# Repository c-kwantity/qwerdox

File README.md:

# Qwerdox Keyboard

Qwerdox is my own fork of the [Kudox keyboard](https://github.com/kumaokobo/kudox-keyboard)

The idea was to learn keyboard PCB design and to design a keyboard with more thumb keys and an additional row of keys that can be mapped to various functions.

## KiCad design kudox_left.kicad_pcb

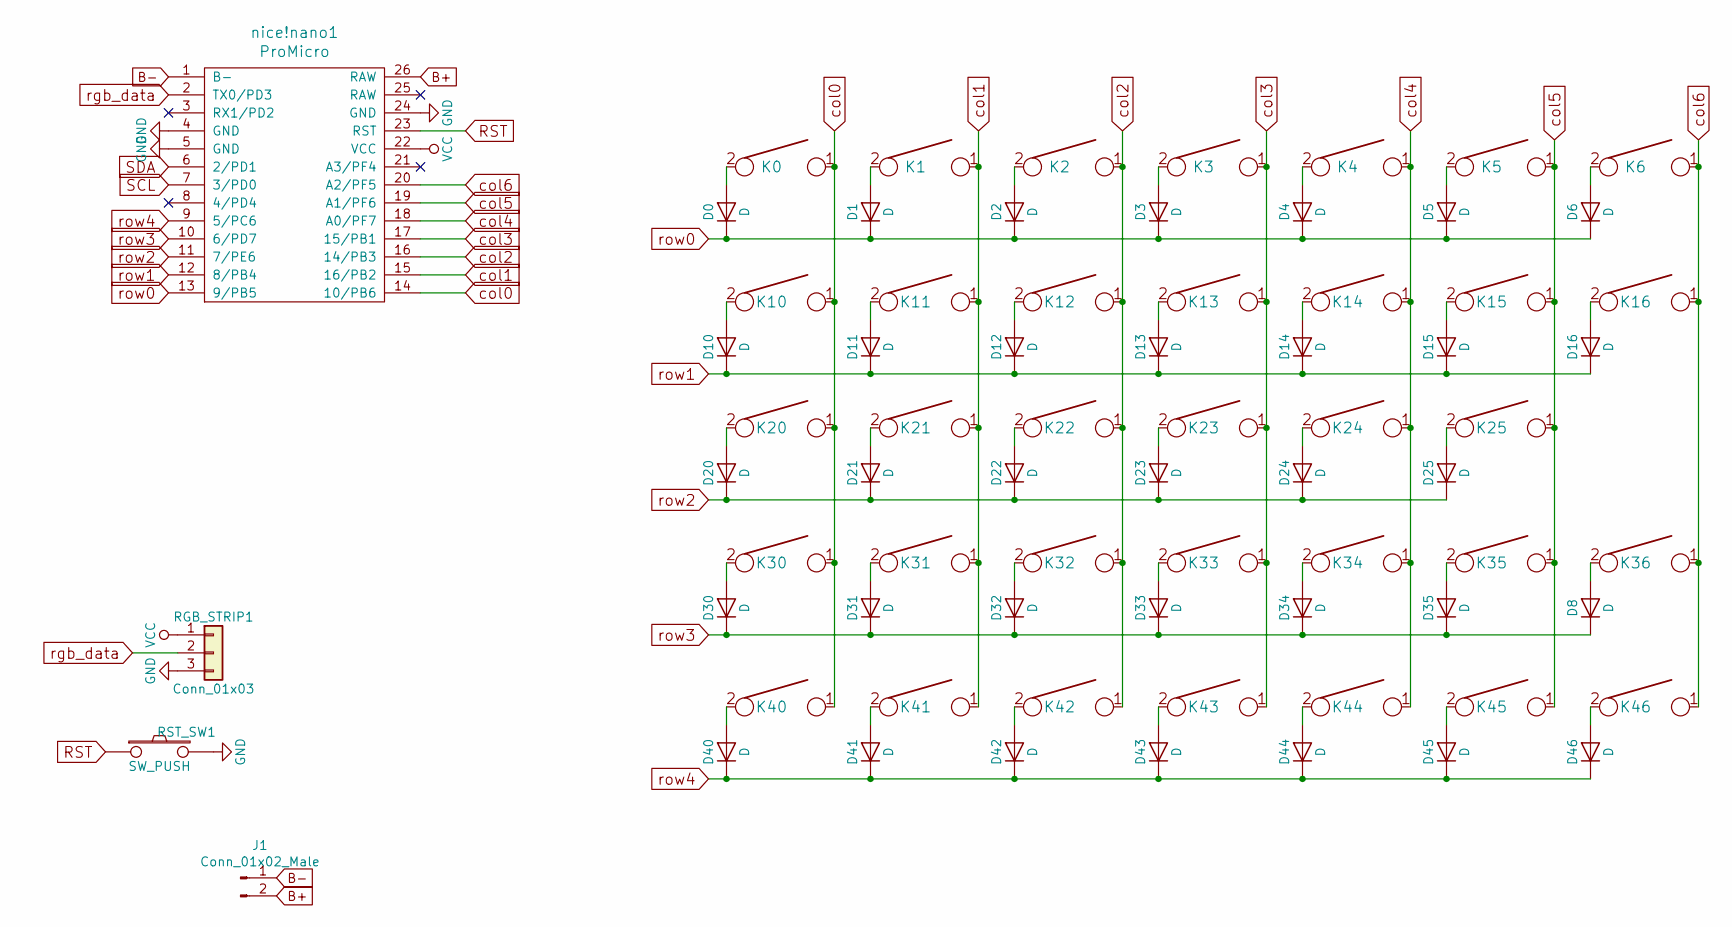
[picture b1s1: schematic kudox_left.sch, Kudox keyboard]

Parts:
D0, D1, D2, D3, D4, D5, D6, D8, D10, D11, D12, D13, D14, D15, D16, D20, D21, D22, D23, D24, D25, D30, D31, D32, D33, D34, D35, D40, D41, D42, D43, D44, D45, D46: D; Diode-dual
J1: Conn_01x02_Male; Molex_KK-254_AE-6410-02A_1x02_P2.54mm_Vertical
K0, K1, K2, K3, K4, K5, K6, K10, K11, K12, K13, K14, K15, K16, K20, K21, K22, K23, K24, K25, K30, K31, K32, K33, K34, K35, K36, K40, K41, K42, K43, K44, K45, K46: KEYSW; MXOnly-1U-Hotswap
RGB_STRIP1: Conn_01x03; Molex_KK-254_AE-6410-03A_1x03_P2.54mm_Vertical
RST_SW1: SW_PUSH; SW_PUSH_6mm_h4.3mm
nice!nano1: ProMicro; ArduinoProMicro

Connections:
B+: J1.2, nice!nano1.26 (RAW)
B-: J1.1, nice!nano1.1 (B-)
GND: RGB_STRIP1.3, RST_SW1.2, nice!nano1.4 (GND), nice!nano1.5 (GND), nice!nano1.24 (GND)
unnamed: D0.2 (A), K0.2
unnamed: D1.2 (A), K1.2
unnamed: D2.2 (A), K2.2
unnamed: D3.2 (A), K3.2
unnamed: D4.2 (A), K4.2
unnamed: D5.2 (A), K5.2
unnamed: D6.2 (A), K6.2
unnamed: D8.2 (A), K36.2
unnamed: D10.2 (A), K10.2
unnamed: D11.2 (A), K11.2
unnamed: D12.2 (A), K12.2
unnamed: D13.2 (A), K13.2
unnamed: D14.2 (A), K14.2
unnamed: D15.2 (A), K15.2
unnamed: D16.2 (A), K16.2
unnamed: D20.2 (A), K20.2
unnamed: D21.2 (A), K21.2
unnamed: D22.2 (A), K22.2
unnamed: D23.2 (A), K23.2
unnamed: D24.2 (A), K24.2
unnamed: D25.2 (A), K25.2
unnamed: D30.2 (A), K30.2
unnamed: D31.2 (A), K31.2
unnamed: D32.2 (A), K32.2
unnamed: D33.2 (A), K33.2
unnamed: D34.2 (A), K34.2
unnamed: D35.2 (A), K35.2
unnamed: D40.2 (A), K40.2
unnamed: D41.2 (A), K41.2
unnamed: D42.2 (A), K42.2
unnamed: D43.2 (A), K43.2
unnamed: D44.2 (A), K44.2
unnamed: D45.2 (A), K45.2
unnamed: D46.2 (A), K46.2
RST: RST_SW1.1, nice!nano1.23 (RST)
VCC: RGB_STRIP1.1, nice!nano1.22 (VCC)
col0: K0.1, K10.1, K20.1, K30.1, K40.1, nice!nano1.14 (10/PB6)
col1: K1.1, K11.1, K21.1, K31.1, K41.1, nice!nano1.15 (16/PB2)
col2: K2.1, K12.1, K22.1, K32.1, K42.1, nice!nano1.16 (14/PB3)
col3: K3.1, K13.1, K23.1, K33.1, K43.1, nice!nano1.17 (15/PB1)
col4: K4.1, K14.1, K24.1, K34.1, K44.1, nice!nano1.18 (A0/PF7)
col5: K5.1, K15.1, K25.1, K35.1, K45.1, nice!nano1.19 (A1/PF6)
col6: K6.1, K16.1, K36.1, K46.1, nice!nano1.20 (A2/PF5)
rgb_data: RGB_STRIP1.2, nice!nano1.2 (TX0/PD3)
row0: D0.1 (K), D1.1 (K), D2.1 (K), D3.1 (K), D4.1 (K), D5.1 (K), D6.1 (K), nice!nano1.13 (9/PB5)
row1: D10.1 (K), D11.1 (K), D12.1 (K), D13.1 (K), D14.1 (K), D15.1 (K), D16.1 (K), nice!nano1.12 (8/PB4)
row2: D20.1 (K), D21.1 (K), D22.1 (K), D23.1 (K), D24.1 (K), D25.1 (K), nice!nano1.11 (7/PE6)
row3: D8.1 (K), D30.1 (K), D31.1 (K), D32.1 (K), D33.1 (K), D34.1 (K), D35.1 (K), nice!nano1.10 (6/PD7)
row4: D40.1 (K), D41.1 (K), D42.1 (K), D43.1 (K), D44.1 (K), D45.1 (K), D46.1 (K), nice!nano1.9 (5/PC6)

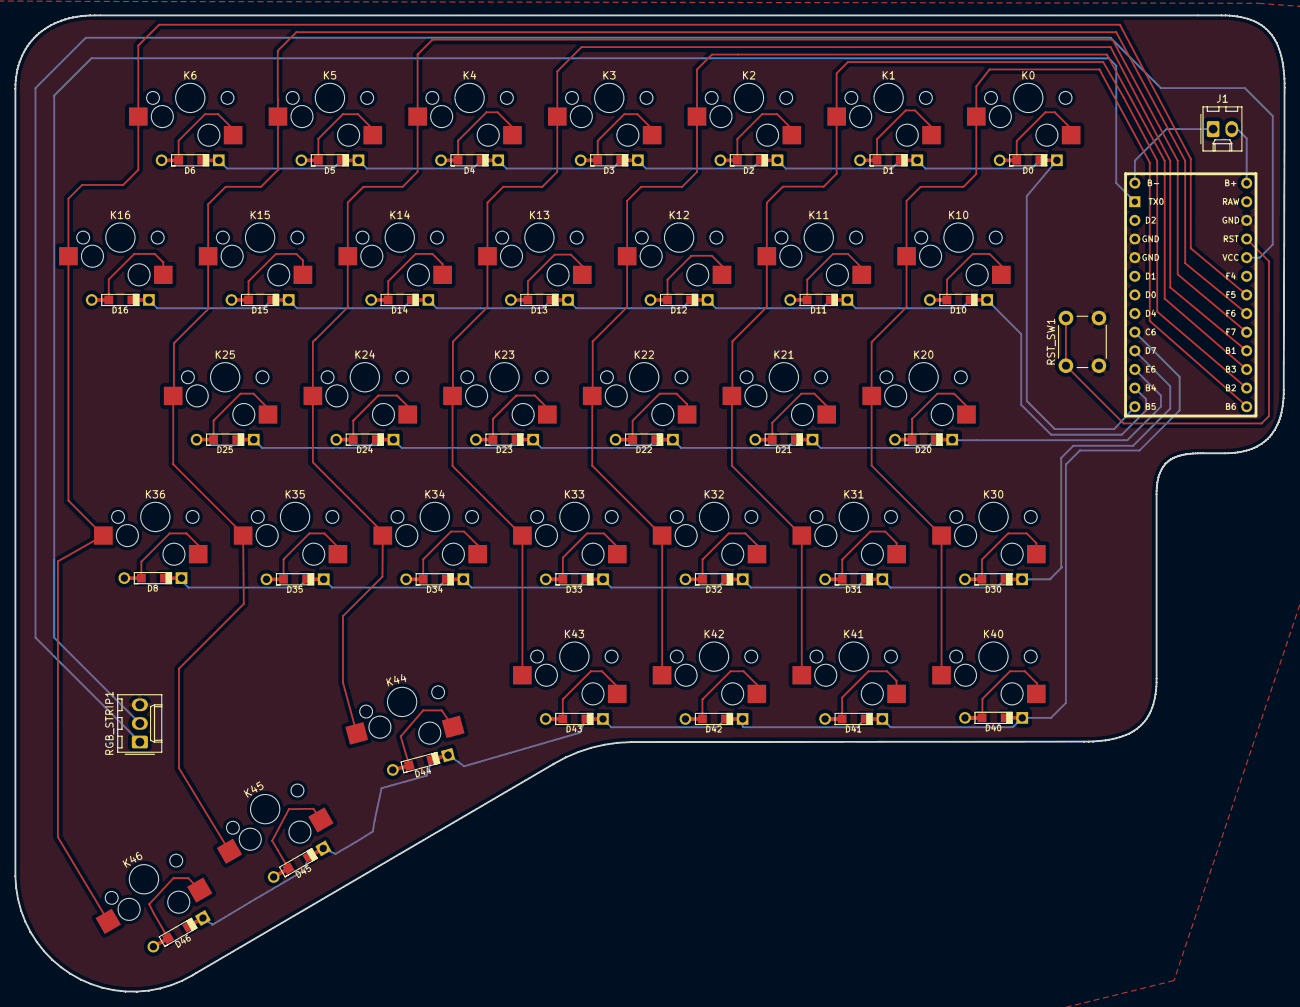
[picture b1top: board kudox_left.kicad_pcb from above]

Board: 2 copper layers, 173.1 x 133.2 mm, 72 parts (0 on the bottom side), 52 nets.

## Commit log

2022-01-28 transer to github
2022-01-28 changing readme
